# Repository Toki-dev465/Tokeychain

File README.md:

# Introduction
I built this project as a fun way to learn more about PCB, CAD and firmware design. I spent quite a lot of time on it and learned a lot especially about CAD modelling. I hope to show it off by hooking it up to my keys and other accessories.

# How it works
The Xiao ESP32-S3 reads tilt from the ADXL345 accelerometer. This is used to create interactive animations displayed on the OLED. As of right now, there is only one "game", the ball game. As you tilt the device the ball starts speeding up in that direction and slows down over time from "friction." The ball also bounces off the edge, which is displayed as a white box. The device will support more of these interactive animations and the animations will be cycled by tap detection on the accelerometer module. This version of the Xiao supports a rechargeable battery with an on-board charging module, which this device will utilize.

# Assembly instructions
1. Insert OLED: Place the OLED in the rectangular cutout on the case.
2. Stack components: Place the PCB and the battery on top of the OLED.
3. Close case: Snap back cover onto the case until it securely clicks in place. 

# Firmware & Flashing

* **ino (arduino) file:** [ball_game.ino](Firmware/ball_game.ino)

1. Install Arduino IDE
2. Add ESP 32 board support: Click on file, preferences, then paste this into the additional board managers URL (https://raw.githubusercontent.com/espressif/arduino-esp32/gh-pages/package_esp32_index.json)
3. Select tools, board, then board manager. Search ESP 32 and install it
4. Select tools, board, esp32, then select Xiao ESP-32-S3 and plug in the device.
5. Hit sketch, then upload 

# Challenges
All went quite smoothly except for the CAD modelling part. I used Fusion only once and that was by following a tutorial. Therefore, this project gave me a massive headache! I had lots of trouble just doing the most basic and minute things such as creating a sketch, projecting onto a sketch, etc. However, due to the immense amount of time I spent, I learned a lot regarding the basics of Fusion and spending so much time on it just made completing the final design more rewarding. I am very proud of how it turned out. 

# PCB design
The schematic and PCB were made using the open-source software KiCad. I made sure to use global net variables for the schematic because otherwise, I would be left with incomprehensible messy wiring. The PCB uses a two-layer system. The top layer (F.Cu) is used for routing traces, whereas the bottom layer (B.Cu) is used for grounding using copper fill zones. I made sure to make the power traces 0.5mm in thickness as recommended by professionals in the industry.

| Schematic | PCB |
|-----------|-----|
|  |  |

### PCB and Schematic files

* **Project:** [Tokeychain.kicad_pro](PCB/Tokeychain.kicad_pro)
* **PCB:** [Tokeychain.kicad_pcb](PCB/Tokeychain.kicad_pcb)
* **Schematic:** [Tokeychain.kicad_sch](PCB/Tokeychain.kicad_sch)
* **Gerbers:** [Tokeychain_Gerbers.zip](PCB/Tokeychain_Gerbers.zip)

# CAD design
The CAD components were built using AutoDesk Fusion software. The components are all inside a 38x50x20 mm 3D-printed case with a key loop at the top and a USB-C cutout at the bottom. The back is covered using a snap-fit cover.

| Fusion Snapshot |
|------------------|
|  |

### CAD & Print Files

* **Preview:** [Tokeychain_assembled.png](CAD%20MODEL/Tokeychain_assembled.png)
* **3D Model:** [Tokeychain.stl](CAD%20MODEL/Tokeychain.stl)
* **Source File:** [Tokeychain_assembled.f3z](CAD%20MODEL/Tokeychain_assembled.f3z)
* **Step file:** [Tokeychain_assembled.step](CAD%20MODEL/Tokeychain_assembled.step)

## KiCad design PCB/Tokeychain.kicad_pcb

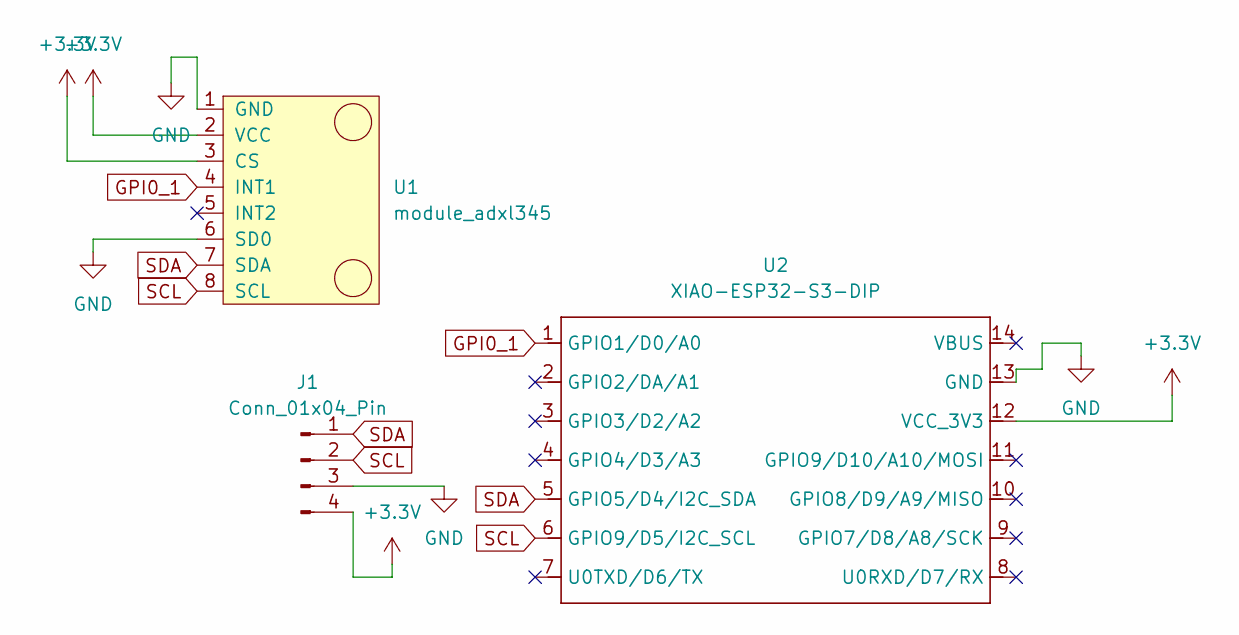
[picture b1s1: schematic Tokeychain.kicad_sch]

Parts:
J1: Conn_01x04_Pin; OLED_SSD1306_I2C_0.96
U1: module_adxl345
U2: XIAO-ESP32-S3-DIP

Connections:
+3.3V: J1.4, U1.2 (VCC), U1.3 (CS), U2.12 (VCC_3V3)
GND: J1.3, U1.1 (GND), U1.6 (SD0), U2.13 (GND)
GPI0_1: U1.4 (INT1), U2.1 (GPIO1/D0/A0)
SCL: J1.2, U1.8 (SCL), U2.6 (GPIO9/D5/I2C_SCL)
SDA: J1.1, U1.7 (SDA), U2.5 (GPIO5/D4/I2C_SDA)

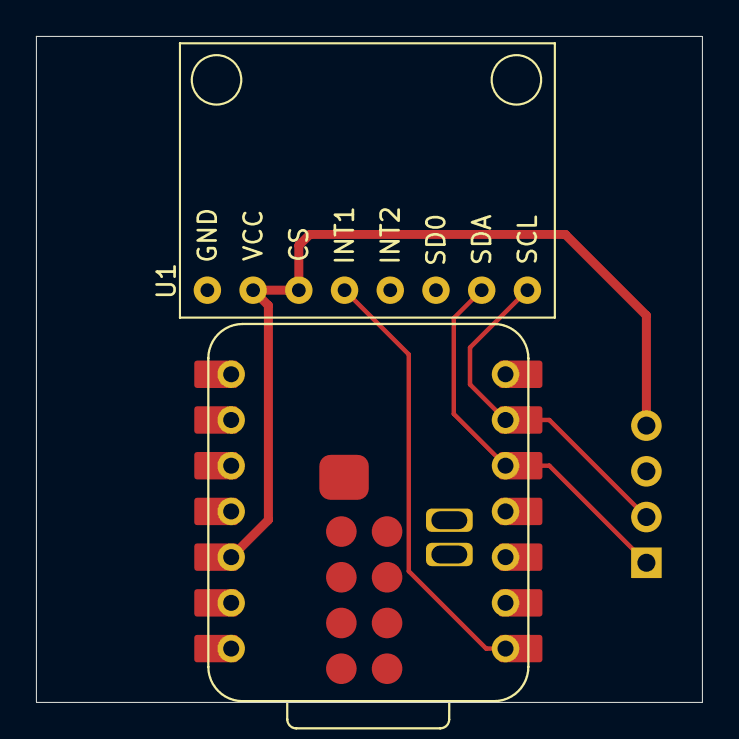
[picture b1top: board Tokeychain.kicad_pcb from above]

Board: 2 copper layers, 37.0 x 37.0 mm, 3 parts (0 on the bottom side), 5 nets.
